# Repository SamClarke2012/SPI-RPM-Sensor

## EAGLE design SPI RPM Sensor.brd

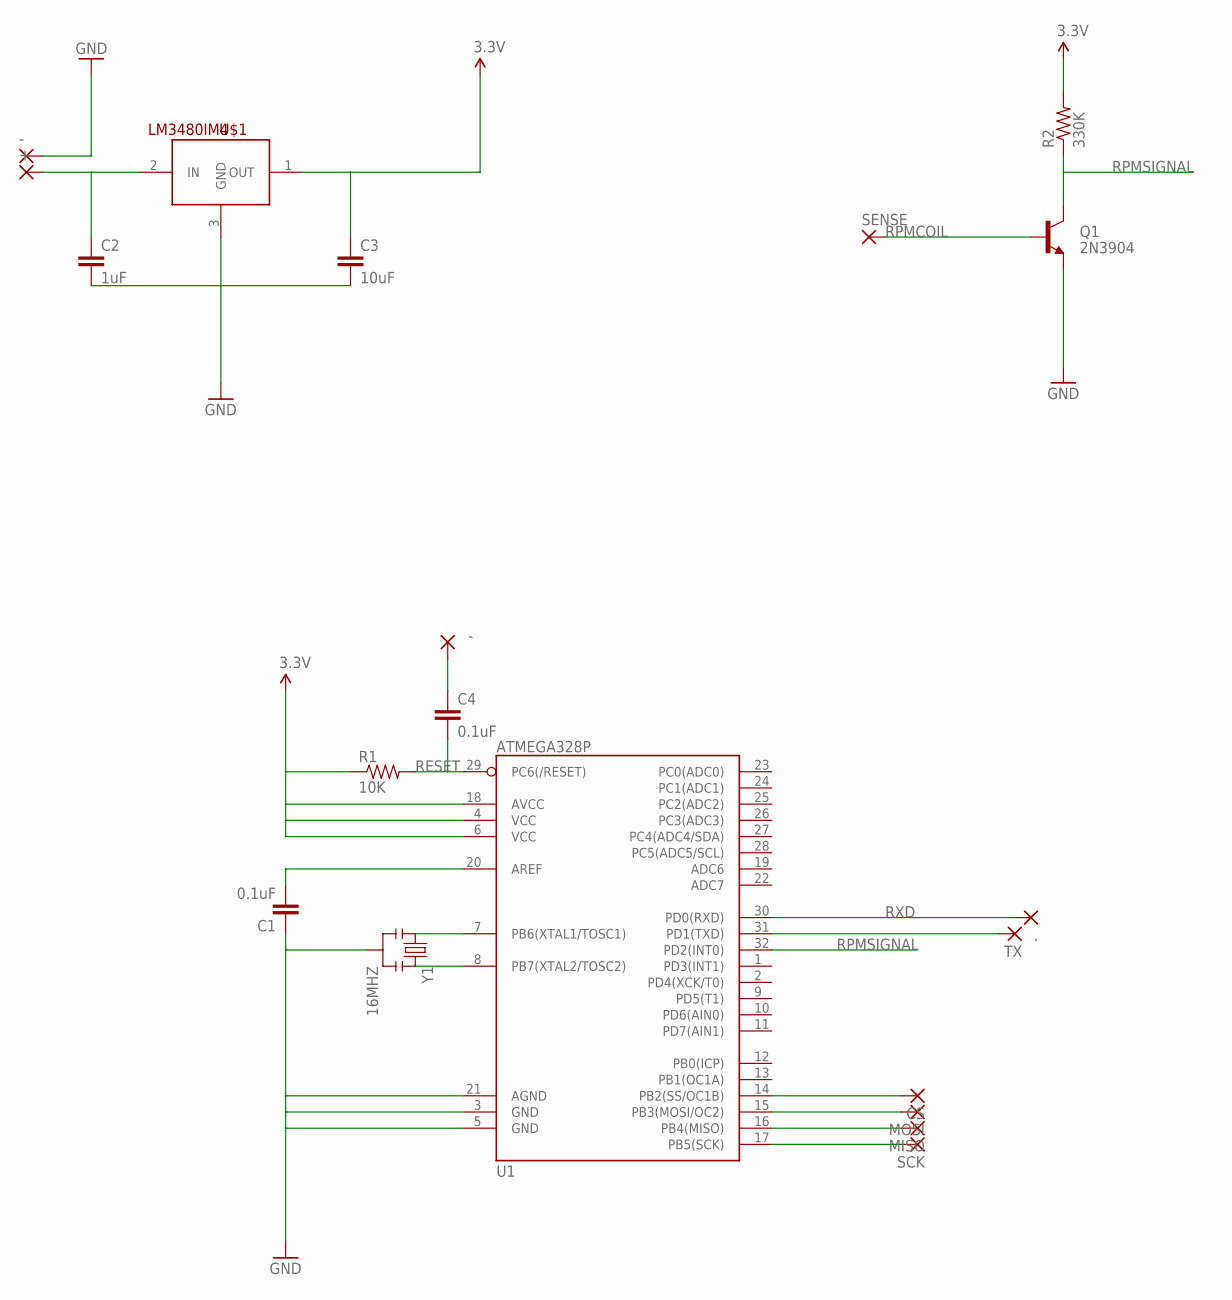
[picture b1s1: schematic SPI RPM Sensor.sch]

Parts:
+: WIREPADSMD5-2,5; 5-2,5
,: WIREPADSMD1,27-254; SMD1,27-2,54
-: WIREPADSMD5-2,5; 5-2,5
.: WIREPADSMD1,27-254; SMD1,27-2,54
C1, C4: 0.1uF; 0603-CAP
C2: 1uF; 0603-CAP
C3: 10uF; 0603-CAP
CS: WIREPADSMD5-2,5; 5-2,5
MISO: WIREPADSMD5-2,5; 5-2,5
MOSI: WIREPADSMD5-2,5; 5-2,5
Q1: 2N3904; TO-92
R1: 10K; 0603-RES
R2: 330K; 0603-RES
SCK: WIREPADSMD5-2,5; 5-2,5
SENSE: WIREPADSMD5-2,5; 5-2,5
TX: WIREPADSMD1,27-254; SMD1,27-2,54
U1: ATMEGA328P; TQFP32-08
U$1: LM3480IM4; SOT23-3
Y1: 16MHZ; RESONATOR-SMD

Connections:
3.3V: C3.1, R1.1, R2.2, U1.4 (VCC), U1.6 (VCC), U1.18 (AVCC), U$1.1 (OUT)
AREF: C1.2, U1.20 (AREF)
CS: CS.1, U1.14 (PB2(SS/OC1B))
GND: -.1, C1.1, C2.2, C3.2, Q1.1 (E), U1.3 (GND), U1.5 (GND), U1.21 (AGND), U$1.3 (GND), Y1.2
MISO: MISO.1, U1.16 (PB4(MISO))
MOSI: MOSI.1, U1.15 (PB3(MOSI/OC2))
unnamed: U1.7 (PB6(XTAL1/TOSC1)), Y1.1
unnamed: U1.8 (PB7(XTAL2/TOSC2)), Y1.3
unnamed: TX.1, U1.31 (PD1(TXD))
unnamed: ,.1, C4.1
RESET: C4.2, R1.2, U1.29 (PC6(/RESET))
RPMCOIL: Q1.2 (B), SENSE.1
RPMSIGNAL: Q1.3 (C), R2.1, U1.32 (PD2(INT0))
RXD: ..1, U1.30 (PD0(RXD))
SCK: SCK.1, U1.17 (PB5(SCK))
VIN: +.1, C2.1, U$1.2 (IN)

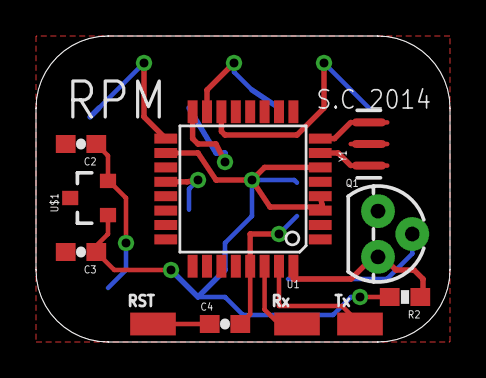
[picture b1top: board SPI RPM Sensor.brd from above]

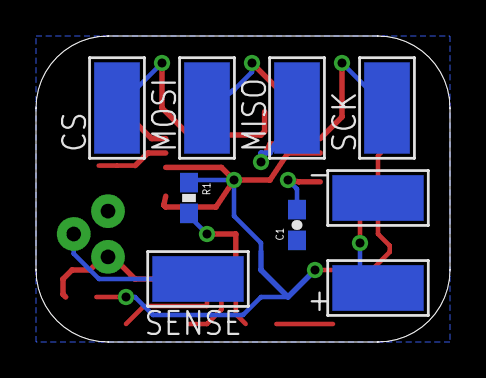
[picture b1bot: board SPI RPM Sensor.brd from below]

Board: 2 copper layers, 23.0 x 17.0 mm, 20 parts (9 on the bottom side), 16 nets.

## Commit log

2014-10-11 init

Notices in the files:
parts and their libraries:
SparkFun-Passives: Licensing: Creative Commons ShareAlike 4.0 International - https://creativecommons.org/licenses/by-sa/4.0
